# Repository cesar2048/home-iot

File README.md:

# Overview

# Features
  * "Configuration mode" starts an AP with a Web server to set parameters
    LED blinks every 5 seconds in this mode
    AP shows as "Hyg00FF" where the last digits are from the mac address
    Configuration page is available at http://192.168.2.1/
    Indicators:
      * LED blink twice: Failed to connect to WiFi
  * "Data aquisition mode" pushes a a new measurement every 1 minute
    Indicators:
      * LED blinks 4 times: Failed to write to InfluxDB
      * LED blinks 3 times: Failed to read from sensor

# References

ESP32 Arduino:
  * [Pinout: ESP32 DevKit 36 & 30 pin](https://www.etechnophiles.com/esp32-dev-board-pinout-specifications-datasheet-and-schematic/)
  * [Pinout: (doit_esp32_devkit-v1_30p) Github/TronixLab](https://github.com/TronixLab/DOIT_ESP32_DevKit-v1_30P)
  * [Pinout: (doit-esp32-devkit-v1) circuitstate.com](https://www.circuitstate.com/pinouts/doit-esp32-devkit-v1-wifi-development-board-pinout-diagram-and-reference/)
  * [Pinout: (AdafruitQTPy)](https://learn.adafruit.com/adafruit-qt-py-esp32-s2/pinouts)
  * [Examples: WiFi Client](https://github.com/espressif/arduino-esp32/blob/master/libraries/WiFi/examples/WiFiClient/WiFiClient.ino)
  * [Examples: AdafuitQT Pins](https://github.com/espressif/arduino-esp32/blob/master/variants/adafruit_qtpy_esp32s2/pins_arduino.h)
  * [Firmware: Install micropython](https://docs.micropython.org/en/latest/esp32/tutorial/intro.html#getting-the-firmware)

ESP32 Tutorials:
  * [ESP32 supress boot messages](https://community.platformio.org/t/esp32-prevent-from-sending-serial-output-at-startup/18756/2)
  * [Preferences](https://github.com/espressif/arduino-esp32/blob/21b88659b9ded3fcc1082f23f498bc2a04cd4f1b/docs/source/tutorials/preferences.rst#L668)
  * [NodeMCU with DHT22](https://simple-circuit.com/esp-12e-nodemcu-ssd1306-dht22-am2302/)

ESP32 DeepSleep:
  * [Deep sleep power consumption](https://www.reddit.com/r/esp32/comments/11yjvvk/deep_sleep_power_consumption_esp32s3_way_too_high/)
  * [Esp32 FireBeetle deep sleep](https://lucidar.me/en/esp32/power-consumption-of-esp32-firebeetle-dfr0478/)
  * [Esp32 DevKitC power consumption](https://lucidar.me/en/esp32/power-consumption-of-esp32-devkitc-v4/)
  * [Wake up from Deep Sleep](https://randomnerdtutorials.com/esp32-external-wake-up-deep-sleep/)
  * [Reading TX w/o USB](https://mischianti.org/2021/03/10/esp32-power-saving-modem-and-light-sleep-2/)

PCBs:
  * [DIY PCB with Toner printer](https://hackaday.com/2016/09/12/take-your-pcbs-from-good-to-great-toner-transfer/)
  * [KiCad tutorial](https://www.youtube.com/watch?v=vaCVh2SAZY4&list=PL3bNyZYHcRSUhUXUt51W6nKvxx2ORvUQB&index=1&pp=iAQB)

Other sources for GPIO reference:

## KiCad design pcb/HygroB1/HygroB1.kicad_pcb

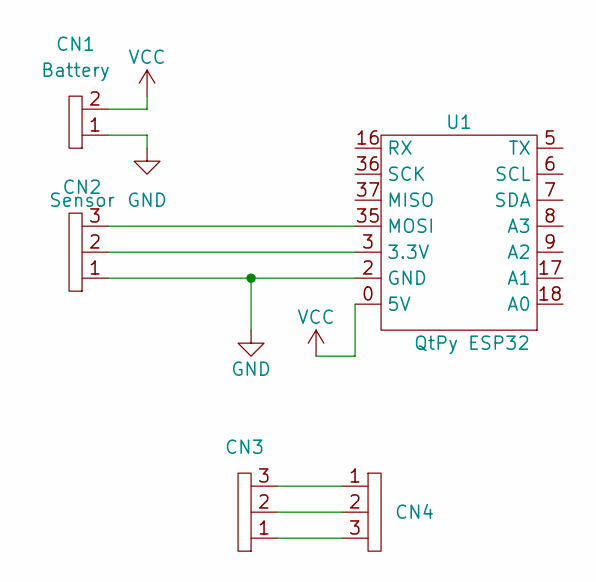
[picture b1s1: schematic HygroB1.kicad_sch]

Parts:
CN1: Battery; FemHeader-2x1
CN2: Sensor; FemHeader-3x1
CN3, CN4: FemHeader-3x1
U1: QtPy ESP32; AdafruitQtPy_ESP32-S2

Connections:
GND: CN1.1, CN2.1, U1.2 (GND)
unnamed: CN3.1, CN4.3
unnamed: CN3.2, CN4.2
unnamed: CN3.3, CN4.1
unnamed: CN2.2, U1.3 (3.3V)
unnamed: CN2.3, U1.35 (MOSI)
VCC: CN1.2, U1.0 (5V)

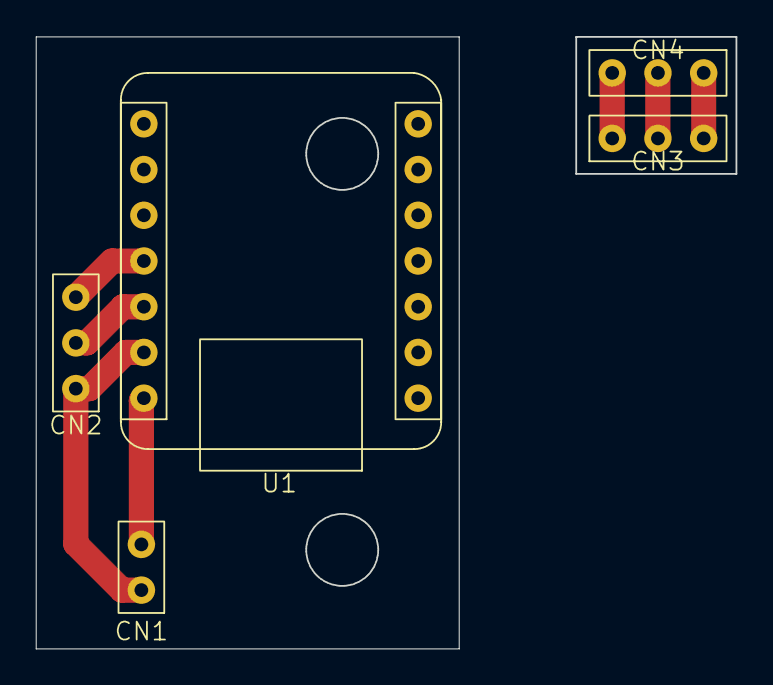
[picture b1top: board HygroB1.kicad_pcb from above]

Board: 2 copper layers, 38.9 x 34.0 mm, 5 parts (0 on the bottom side), 7 nets.

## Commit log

2023-06-21 initial commmit
2023-06-21 add wifi client and server
2023-06-21 docs: reference links and reference GPIO
2023-06-27 Add InfluxDB test code
2023-07-13 Add 3d mechanical assembly designs
2023-07-13 Changed to use deep sleep instead of simple delay
2023-07-13 Reduce messages, simplify logic
2023-07-15 Add blinking indicator
2023-08-02 add test wifi AP and refactor app code
2023-08-02 add adafruit boards and 1551V1BK enclosure
2023-08-03 add wifi configuration via html page
2023-08-03 add sensor reading logic
2023-08-04 improve html page style and add influx fields
2023-08-04 add reset for failure count
2023-08-05 add influx configuration to preferences
2023-08-30 parameterize indicator led for adafruit esp32
2023-09-02 ux: add packaging sketches
2023-09-10 improve html interface
2023-09-10 add blink state when on wifi server
2023-09-11 add device name customization
2023-09-14 Improve battery assembly design, add TP4056
2023-09-17 long press to desconfigure and use neopixel on qt
2023-09-17 add pcb designs
2023-09-24 add bluetooth server (too big)
2023-09-24 reduce binary under 1.5Mb
2023-09-24 add ble server and client
2023-09-25 tinypico support plus debug code
2023-09-26 turn on leds when debug pin
2023-09-27 ble client restarts after reading
2023-10-03 change to AHT20, adapt to QtPy Pico
